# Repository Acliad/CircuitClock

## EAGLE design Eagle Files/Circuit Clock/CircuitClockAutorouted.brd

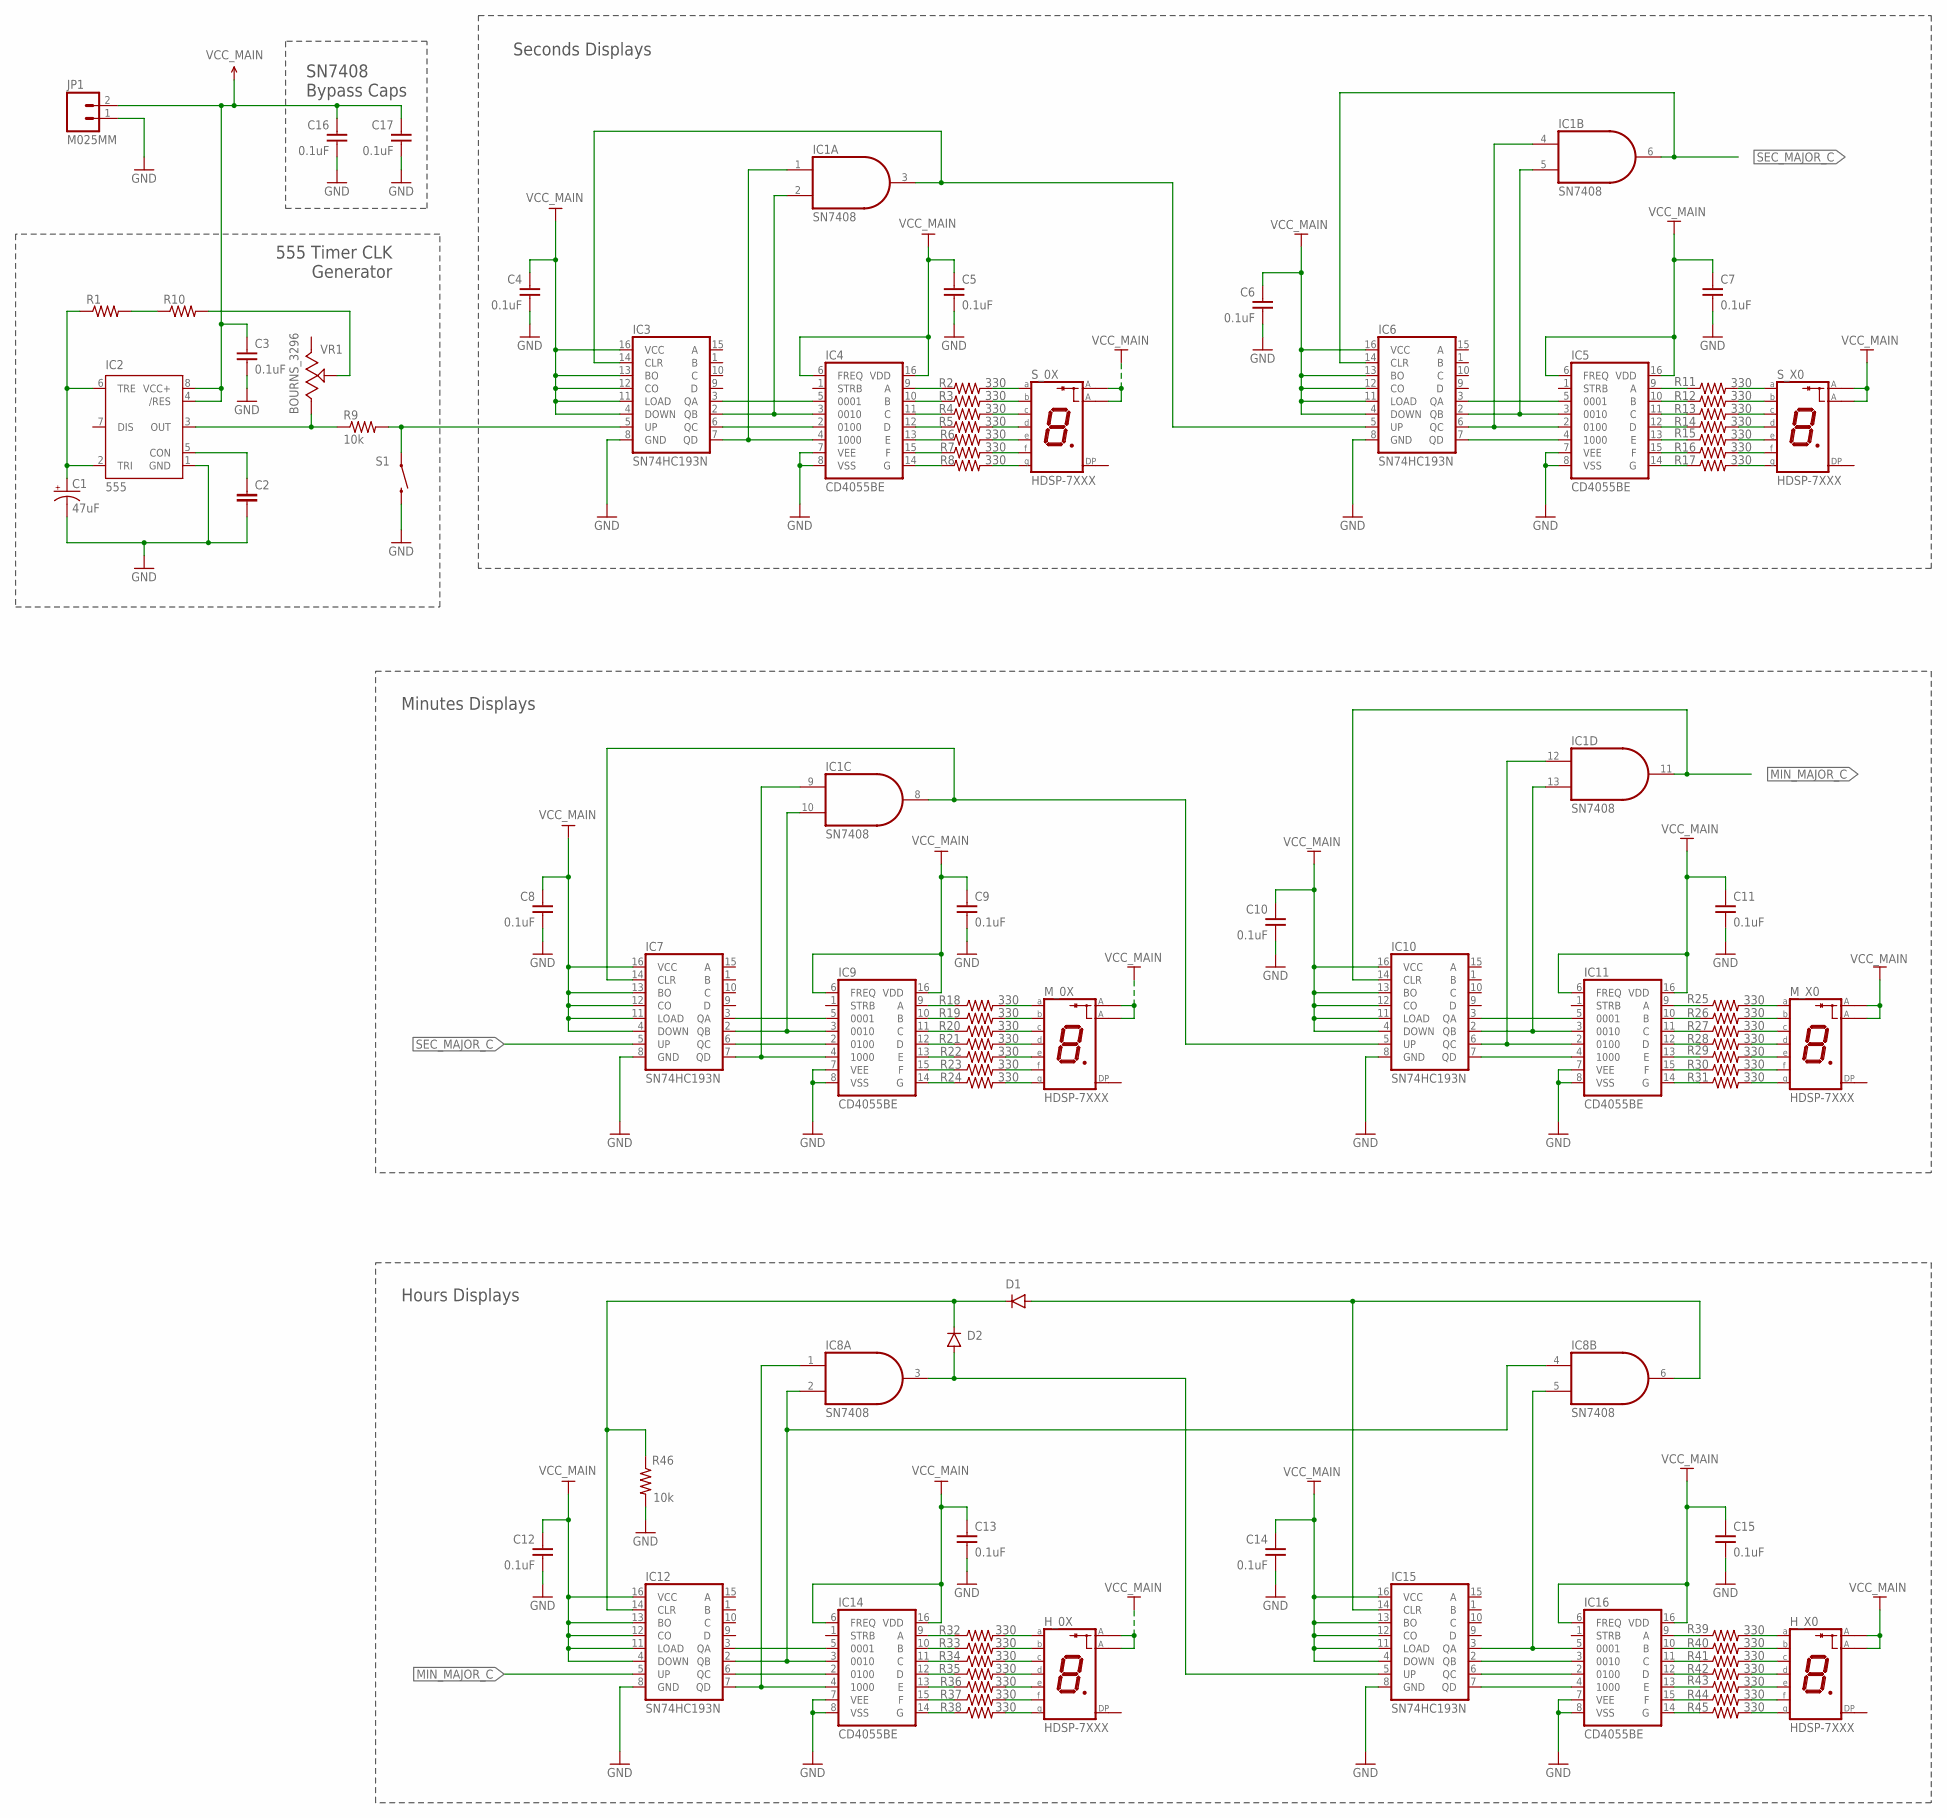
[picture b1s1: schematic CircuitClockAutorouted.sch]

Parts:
C1: 47uF; 2.54MM_LEAD-6.3MM_DIA
C2: CAPPTH; CAP-PTH-SMALL
C3, C4, C5, C6, C7, C8, C9, C10, C11, C12, C13, C14, C15, C16, C17: 0.1uF; 2.54MM_LEAD
D1, D2: THROUGH_HOLE_DO-35; DO35-10
H_0X: HDSP-7XXX
H_X0: HDSP-7XXX
IC1, IC8: SN7408; DIL14
IC2: 555; DIP08-KIT
IC3, IC6, IC7, IC10, IC12, IC15: SN74HC193N; DIL16
IC4, IC5, IC9, IC11, IC14, IC16: CD4055BE; DIL16
JP1: M025MM; SCREWTERMINAL-5MM-2
M_0X: HDSP-7XXX
M_X0: HDSP-7XXX
R1, R10: RESISTORAXIAL-0.3; AXIAL-0.3
R2, R3, R4, R5, R6, R7, R8, R11, R12, R13, R14, R15, R16, R17, R18, R19, R20, R21, R22, R23, R24, R25, R26, R27, R28, R29, R30, R31, R32, R33, R34, R35, R36, R37, R38, R39, R40, R41, R42, R43, R44, R45: 330; 1/4W_0.3
R9: 10k; AXIAL-0.3
R46: 10k; 1/4W_0.3
S1: SWITCH-MOMENTARY-2PTH; TACTILE-PTH
S_0X: HDSP-7XXX
S_X0: HDSP-7XXX
VR1: BOURNS_3296; 3296

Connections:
CLK: IC3.5 (UP), R9.P$2 (2), S1.1
GND: C1.-, C2.2, C3.2, C4.2, C5.2, C6.2, C7.2, C8.2, C9.2, C10.2, C11.2, C12.2, C13.2, C14.2, C15.2, C16.2, C17.2, IC1.7 (GND), IC2.1 (GND), IC3.8 (GND), IC4.7 (VEE), IC4.8 (VSS), IC5.7 (VEE), IC5.8 (VSS), IC6.8 (GND), IC7.8 (GND), IC8.7 (GND), IC9.7 (VEE), IC9.8 (VSS), IC10.8 (GND), IC11.7 (VEE), IC11.8 (VSS), IC12.8 (GND), IC14.7 (VEE), IC14.8 (VSS), IC15.8 (GND), IC16.7 (VEE), IC16.8 (VSS), JP1.1, R46.P$2 (2), S1.3 (2)
HR_MAJOR_C: D1.C, D2.C, IC12.14 (CLR), R46.P$1 (1)
HR_MINOR_C: D2.A, IC8.3 (O), IC15.5 (UP)
MIN_MAJOR_C: IC1.11 (O), IC10.14 (CLR), IC12.5 (UP)
MIN_MINOR_C: IC1.8 (O), IC7.14 (CLR), IC10.5 (UP)
unnamed: IC1.4 (I0), IC5.2 (0100), IC6.6 (QC)
unnamed: C1.+, IC2.2 (TRI), IC2.6 (TRE), R1.P$1 (1)
unnamed: IC3.3 (QA), IC4.5 (0001)
unnamed: C2.1, IC2.5 (CON)
unnamed: IC1.2 (I1), IC3.2 (QB), IC4.3 (0010)
unnamed: IC1.5 (I1), IC5.3 (0010), IC6.2 (QB)
unnamed: IC7.3 (QA), IC9.5 (0001)
unnamed: IC4.9 (A), R2.P$1 (1)
unnamed: IC4.10 (B), R3.P$1 (1)
unnamed: IC4.11 (C), R4.P$1 (1)
unnamed: IC4.12 (D), R5.P$1 (1)
unnamed: IC4.13 (E), R6.P$1 (1)
unnamed: IC4.15 (F), R7.P$1 (1)
unnamed: IC4.14 (G), R8.P$1 (1)
unnamed: IC2.3 (OUT), R9.P$1 (1), VR1.1 (A)
unnamed: R2.P$2 (2), S_0X.P$10 (A)
unnamed: R3.P$2 (2), S_0X.P$9 (B)
unnamed: R4.P$2 (2), S_0X.P$8 (C)
unnamed: R5.P$2 (2), S_0X.P$5 (D)
unnamed: R6.P$2 (2), S_0X.P$4 (E)
unnamed: R7.P$2 (2), S_0X.P$2 (F)
unnamed: R8.P$2 (2), S_0X.P$3 (G)
unnamed: R1.P$2 (2), R10.P$1 (1)
unnamed: R10.P$2 (2), VR1.2 (S)
unnamed: IC1.1 (I0), IC3.7 (QD), IC4.4 (1000)
unnamed: IC9.9 (A), R18.P$1 (1)
unnamed: IC5.4 (1000), IC6.7 (QD)
unnamed: IC5.5 (0001), IC6.3 (QA)
unnamed: IC3.6 (QC), IC4.2 (0100)
unnamed: IC5.9 (A), R11.P$1 (1)
unnamed: IC5.10 (B), R12.P$1 (1)
unnamed: IC5.11 (C), R13.P$1 (1)
unnamed: IC5.12 (D), R14.P$1 (1)
unnamed: IC5.13 (E), R15.P$1 (1)
unnamed: IC5.15 (F), R16.P$1 (1)
unnamed: IC5.14 (G), R17.P$1 (1)
unnamed: R11.P$2 (2), S_X0.P$10 (A)
unnamed: R12.P$2 (2), S_X0.P$9 (B)
unnamed: R13.P$2 (2), S_X0.P$8 (C)
unnamed: R14.P$2 (2), S_X0.P$5 (D)
unnamed: R15.P$2 (2), S_X0.P$4 (E)
unnamed: R16.P$2 (2), S_X0.P$2 (F)
unnamed: R17.P$2 (2), S_X0.P$3 (G)
unnamed: IC9.10 (B), R19.P$1 (1)
unnamed: IC9.11 (C), R20.P$1 (1)
unnamed: IC9.12 (D), R21.P$1 (1)
unnamed: IC9.13 (E), R22.P$1 (1)
unnamed: IC9.15 (F), R23.P$1 (1)
unnamed: IC9.14 (G), R24.P$1 (1)
unnamed: M_0X.P$10 (A), R18.P$2 (2)
unnamed: M_0X.P$9 (B), R19.P$2 (2)
unnamed: M_0X.P$8 (C), R20.P$2 (2)
unnamed: M_0X.P$5 (D), R21.P$2 (2)
unnamed: M_0X.P$4 (E), R22.P$2 (2)
unnamed: M_0X.P$2 (F), R23.P$2 (2)
unnamed: M_0X.P$3 (G), R24.P$2 (2)
unnamed: IC10.3 (QA), IC11.5 (0001)
unnamed: IC11.9 (A), R25.P$1 (1)
unnamed: IC11.10 (B), R26.P$1 (1)
unnamed: IC11.11 (C), R27.P$1 (1)
unnamed: IC11.12 (D), R28.P$1 (1)
unnamed: IC11.13 (E), R29.P$1 (1)
unnamed: IC11.15 (F), R30.P$1 (1)
unnamed: IC11.14 (G), R31.P$1 (1)
unnamed: M_X0.P$10 (A), R25.P$2 (2)
unnamed: M_X0.P$9 (B), R26.P$2 (2)
unnamed: M_X0.P$8 (C), R27.P$2 (2)
unnamed: M_X0.P$5 (D), R28.P$2 (2)
unnamed: M_X0.P$4 (E), R29.P$2 (2)
unnamed: M_X0.P$2 (F), R30.P$2 (2)
unnamed: M_X0.P$3 (G), R31.P$2 (2)
unnamed: IC10.7 (QD), IC11.4 (1000)
unnamed: IC7.6 (QC), IC9.2 (0100)
unnamed: IC1.12 (I0), IC10.6 (QC), IC11.2 (0100)
unnamed: IC1.13 (I1), IC10.2 (QB), IC11.3 (0010)
unnamed: IC1.9 (I0), IC7.7 (QD), IC9.4 (1000)
unnamed: IC1.10 (I1), IC7.2 (QB), IC9.3 (0010)
unnamed: IC12.3 (QA), IC14.5 (0001)
unnamed: IC14.9 (A), R32.P$1 (1)
unnamed: IC14.10 (B), R33.P$1 (1)
unnamed: IC14.11 (C), R34.P$1 (1)
unnamed: IC14.12 (D), R35.P$1 (1)
unnamed: IC14.13 (E), R36.P$1 (1)
unnamed: IC14.15 (F), R37.P$1 (1)
unnamed: IC14.14 (G), R38.P$1 (1)
unnamed: H_0X.P$10 (A), R32.P$2 (2)
unnamed: H_0X.P$9 (B), R33.P$2 (2)
unnamed: H_0X.P$8 (C), R34.P$2 (2)
unnamed: H_0X.P$5 (D), R35.P$2 (2)
unnamed: H_0X.P$4 (E), R36.P$2 (2)
unnamed: H_0X.P$2 (F), R37.P$2 (2)
unnamed: H_0X.P$3 (G), R38.P$2 (2)
unnamed: IC16.9 (A), R39.P$1 (1)
unnamed: IC16.10 (B), R40.P$1 (1)
unnamed: IC16.11 (C), R41.P$1 (1)
unnamed: IC16.12 (D), R42.P$1 (1)
unnamed: IC16.13 (E), R43.P$1 (1)
unnamed: IC16.15 (F), R44.P$1 (1)
unnamed: IC16.14 (G), R45.P$1 (1)
unnamed: H_X0.P$10 (A), R39.P$2 (2)
unnamed: H_X0.P$9 (B), R40.P$2 (2)
unnamed: H_X0.P$8 (C), R41.P$2 (2)
unnamed: H_X0.P$5 (D), R42.P$2 (2)
unnamed: H_X0.P$4 (E), R43.P$2 (2)
unnamed: H_X0.P$2 (F), R44.P$2 (2)
unnamed: H_X0.P$3 (G), R45.P$2 (2)
unnamed: IC15.7 (QD), IC16.4 (1000)
unnamed: IC12.6 (QC), IC14.2 (0100)
unnamed: IC15.6 (QC), IC16.2 (0100)
unnamed: IC15.2 (QB), IC16.3 (0010)
unnamed: IC8.1 (I0), IC12.7 (QD), IC14.4 (1000)
unnamed: IC8.2 (I1), IC8.4 (I0), IC12.2 (QB), IC14.3 (0010)
unnamed: D1.A, IC8.6 (O), IC15.14 (CLR)
unnamed: IC8.5 (I1), IC15.3 (QA), IC16.5 (0001)
SEC_MAJOR_C: IC1.6 (O), IC6.14 (CLR), IC7.5 (UP)
SEC_MINOR_C: IC1.3 (O), IC3.14 (CLR), IC6.5 (UP)
VCC: IC1.14 (VCC), IC8.14 (VCC)
VCC_MAIN: C3.1, C4.1, C5.1, C6.1, C7.1, C8.1, C9.1, C10.1, C11.1, C12.1, C13.1, C14.1, C15.1, C16.1, C17.1, H_0X.P$1 (A), H_0X.P$6 (A), H_X0.P$1 (A), H_X0.P$6 (A), IC2.4 (/RES), IC2.8 (VCC+), IC3.4 (DOWN), IC3.11 (LOAD), IC3.12 (CO), IC3.13 (BO), IC3.16 (VCC), IC4.6 (FREQ), IC4.16 (VDD), IC5.6 (FREQ), IC5.16 (VDD), IC6.4 (DOWN), IC6.11 (LOAD), IC6.12 (CO), IC6.13 (BO), IC6.16 (VCC), IC7.4 (DOWN), IC7.11 (LOAD), IC7.12 (CO), IC7.13 (BO), IC7.16 (VCC), IC9.6 (FREQ), IC9.16 (VDD), IC10.4 (DOWN), IC10.11 (LOAD), IC10.12 (CO), IC10.13 (BO), IC10.16 (VCC), IC11.6 (FREQ), IC11.16 (VDD), IC12.4 (DOWN), IC12.11 (LOAD), IC12.12 (CO), IC12.13 (BO), IC12.16 (VCC), IC14.6 (FREQ), IC14.16 (VDD), IC15.4 (DOWN), IC15.11 (LOAD), IC15.12 (CO), IC15.13 (BO), IC15.16 (VCC), IC16.6 (FREQ), IC16.16 (VDD), JP1.2, M_0X.P$1 (A), M_0X.P$6 (A), M_X0.P$1 (A), M_X0.P$6 (A), S_0X.P$1 (A), S_0X.P$6 (A), S_X0.P$1 (A), S_X0.P$6 (A)

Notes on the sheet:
555 Timer CLK Generator
Seconds Displays
Minutes Displays
Hours Displays
SN7408 Bypass Caps

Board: 2 copper layers, 89 parts (0 on the bottom side), 124 nets, no tracks yet.

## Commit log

2019-10-27 Initial commit
    Changes to be committed:
    new file: .DS_Store
    new file: Board Image.png
    new file: CAMOutputs/.DS_Store
    new file: CAMOutputs/Assembly/CircuitClockHandLayout.txt
    new file: CAMOutputs/DrillFiles/drill_1_16.xln

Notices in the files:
parts and their libraries:
SparkFun-Capacitors: Licensing: Creative Commons ShareAlike 4.0 International - https://creativecommons.org/licenses/by-sa/4.0
